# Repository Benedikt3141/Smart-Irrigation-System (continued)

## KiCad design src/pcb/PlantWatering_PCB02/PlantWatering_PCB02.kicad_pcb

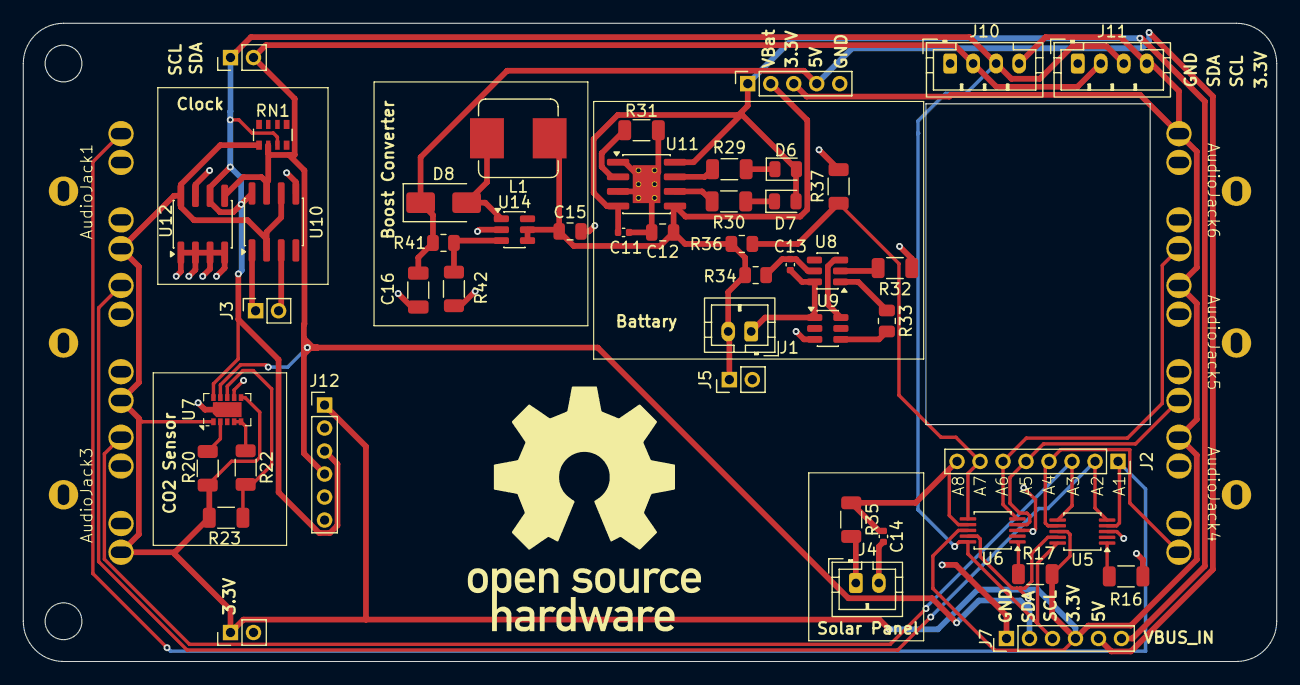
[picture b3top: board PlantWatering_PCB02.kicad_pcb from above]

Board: 2 copper layers, 109.0 x 55.5 mm, 56 parts (0 on the bottom side), 36 nets.

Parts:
AudioJack1, AudioJack2, AudioJack3, AudioJack4, AudioJack5, AudioJack6: PJ-3126-5A
C11, C13, C14: 100nF; C_0402_1005Metric
C12, C15: 10uF; C_0805_2012Metric
C16: 22uF; C_1206_3216Metric
D6: RED; LED_0805_2012Metric
D7: GREEN; LED_0805_2012Metric
D8: SS14; D_SMA
H1, H2: MountingHole; MountingHole_3.2mm_M3
J1: Battery connection; JST_PH_B2B-PH-K_1x02_P2.00mm_Vertical
J2: AnalogSignals; PinSocket_1x08_P2.00mm_Vertical
J3: 32KHZ/SQW; PinSocket_1x02_P2.00mm_Vertical
J4: Solar Panel; JST_PH_B2B-PH-K_1x02_P2.00mm_Vertical
J5: Power output; PinHeader_1x02_P2.00mm_Vertical
J6: Signal Sockets; PinSocket_1x05_P2.00mm_Vertical
J7: Connector to other Board; PinHeader_1x06_P2.00mm_Vertical
J8: I2C; PinHeader_1x02_P2.00mm_Vertical
J9: PWR_Output; PinHeader_1x02_P2.00mm_Vertical
J10, J11: I2C Pins; JST_PH_B4B-PH-K_1x04_P2.00mm_Vertical
J12: Conn_01x06_Socket; PinHeader_1x06_P2.00mm_Vertical
L1: 22uH; L_Bourns_SRP7028A_7.3x6.6mm
R16, R17, R20, R22, R31, R42: 10k; R_1206_3216Metric
R23, R37: 100k; R_1206_3216Metric
R29, R30, R32: 1k; R_1206_3216Metric
R33: 0R; R_0805_2012Metric
R34: 100; R_0805_2012Metric
R35: 4.7k; R_1206_3216Metric
R36: 220k; R_0805_2012Metric
R41: 73.2k; R_0805_2012Metric
RN1: 4.7k Resistor Array; R_Array_Convex_4x0603
U5, U6: ADS1115IDGS; TSSOP-10_3x3mm_P0.5mm
U7: CCS811; AMS_LGA-10-1EP_2.7x4mm_P0.6mm
U8: DW01A; SOT-23-6
U9: FS8205A; SOT-23-6
U10: DS3231MZ; SOIC-8_3.9x4.9mm_P1.27mm
U11: TP4056-42-ESOP8; SOIC-8-1EP_3.9x4.9mm_P1.27mm_EP2.41x3.3mm_ThermalVias
U12: AT24CS32-SSHM; SOIC-8_3.9x4.9mm_P1.27mm
U14: MT3608; SOT-23-6

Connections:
+3.3V: AudioJack1.5 (VCC), AudioJack2.5 (VCC), AudioJack3.5 (VCC), AudioJack4.5 (VCC), AudioJack5.5 (VCC), AudioJack6.5 (VCC), J6.3, J7.4, J9.1, J10.4, J11.4, J12.1, R17.2, R20.2, R23.1, RN1.1 (common), U5.8 (VDD), U6.8 (VDD), U7.1 (ADDR), U7.6 (VDD), U10.2 (VCC), U10.6 (VBAT), U12.8 (VCC)
+5V: C16.1, D8.1 (K), J6.4, J7.5, R41.1
/Analog1: AudioJack1.2 (Analog_Signal), J2.1, U5.4 (AIN0)
/Analog2: AudioJack2.2 (Analog_Signal), J2.2, U5.5 (AIN1)
/Analog3: AudioJack3.2 (Analog_Signal), J2.3, U5.6 (AIN2)
/Analog4: AudioJack4.2 (Analog_Signal), J2.4, U5.7 (AIN3)
/Analog5: AudioJack5.2 (Analog_Signal), J2.5, U6.4 (AIN0)
/Analog6: AudioJack6.2 (Analog_Signal), J2.6, U6.5 (AIN1)
/Analog7: J2.7, R36.2, R37.1, U6.6 (AIN2)
/Analog8: C14.1, J2.8, R35.1, U6.7 (AIN3)
/G1: U8.3 (OC), U9.6 (G1)
/G2: R33.2, U9.4 (G2)
/OC: R33.1, U8.1 (OD)
/S1: C13.2, J1.1, U8.6 (GND), U9.1 (S1)
/SCL: J7.3, J8.1, J10.3, J11.3, J12.3, RN1.3 (R2), U5.10 (SCL), U6.10 (SCL), U7.10 (SCL), U10.8 (SCL), U12.6 (SCL)
/SDA: J7.2, J8.2, J10.2, J11.2, J12.4, RN1.2 (R1), U5.9 (SDA), U6.9 (SDA), U7.9 (SDA), U10.7 (SDA), U12.5 (SDA)
/VBUS_IN: C11.1, D6.2 (A), D7.2 (A), J6.1, J7.6, U11.4 (V_{CC}), U11.8 (CE)
/VBat: C12.1, C15.1, J1.2, J5.1, J6.2, L1.1, R34.1, R36.1, U11.5 (BAT), U14.4 (EN), U14.5 (IN)
GND: AudioJack1.1 (GND), AudioJack2.1 (GND), AudioJack3.1 (GND), AudioJack4.1 (GND), AudioJack5.1 (GND), AudioJack6.1 (GND), C11.2, C12.2, C14.2, C15.2, C16.2, J4.2, J5.2, J6.5, J7.1, J9.2, J10.1, J11.1, J12.2, R16.2, R31.2, R32.1, R37.2, R42.2, U5.3 (GND), U6.3 (GND), U7.7 (~WAKE), U7.11 (GND), U9.3 (S2), U10.5 (GND), U11.1 (TEMP), U11.3 (GND), U11.9 (EPAD), U12.1 (A0), U12.2 (A1), U12.3 (A2), U12.4 (GND), U12.7 (WP), U14.2 (GND)
unnamed: D6.1 (K), R29.1
unnamed: D7.1 (K), R30.1
unnamed: D8.2 (A), L1.2, U14.1 (SW)
unnamed: J3.1, U10.1 (32KHZ)
unnamed: J3.2, U10.3 (~INT/SQW)
unnamed: J4.1, R35.2
unnamed: R16.1, U5.1 (ADDR)
unnamed: R17.1, U6.1 (ADDR)
unnamed: R22.2, R23.2, U7.8 (AUX)
unnamed: R22.1, U7.4 (PWM), U7.5 (Sense)
unnamed: R20.1, U7.2 (~RESET)
unnamed: R32.2, U8.2 (CS)
unnamed: C13.1, R34.2, U8.5 (VCC)
unnamed: R31.1, U11.2 (PROG)
unnamed: R29.2, U11.7 (~CHRG)
unnamed: R30.2, U11.6 (~STDBY)
unnamed: R41.2, R42.1, U14.3 (FB)

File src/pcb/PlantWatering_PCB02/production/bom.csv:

"Reference","Qty","Value","DNP","Exclude from BOM","Exclude from Board","Footprint","LCSC PN"
"AudioJack1,AudioJack2,AudioJack3,AudioJack4,AudioJack5,AudioJack6","6","","","","","ESP32_NodeMCU:PJ-3126-5A","C145816"
"C11,C13,C14","3","100nF","","","","Capacitor_SMD:C_0402_1005Metric","C1525"
"C12,C15","2","10uF","","","","Capacitor_SMD:C_0805_2012Metric","C1713"
"C16","1","22uF","","","","Capacitor_SMD:C_1206_3216Metric","C5672"
"D6","1","RED","","","","LED_SMD:LED_0805_2012Metric","C84256"
"D7","1","GREEN","","","","LED_SMD:LED_0805_2012Metric","C84260"
"D8","1","SS14","","","","Diode_SMD:D_SMA","C2480"
"L1","1","22uH","","","","Inductor_SMD:L_Bourns_SRP7028A_7.3x6.6mm","C2838326"
"R16,R17,R20,R22,R31,R42","6","10k","","","","Resistor_SMD:R_1206_3216Metric","C1489"
"R23,R37","2","100k","","","","Resistor_SMD:R_1206_3216Metric","C17900"
"R29,R30,R32","3","1k","","","","Resistor_SMD:R_1206_3216Metric","C4410"
"R33","1","0R","","","","Resistor_SMD:R_0805_2012Metric","C17477"
"R34","1","100","","","","Resistor_SMD:R_0805_2012Metric","C17408"
"R35","1","4.7k","","","","Resistor_SMD:R_1206_3216Metric","C17936"
"R36","1","220k","","","","Resistor_SMD:R_0805_2012Metric","C17556"
"R41","1","73.2k","","","","Resistor_SMD:R_0805_2012Metric","C17814"
"RN1","1","4.7k Resistor Array","","","","Resistor_SMD:R_Array_Convex_4x0603","C1980"
"U5,U6","2","ADS1115IDGS","","","","Package_SO:TSSOP-10_3x3mm_P0.5mm","C37593"
"U8","1","DW01A","","","","Package_TO_SOT_SMD:SOT-23-6","C351410"
"U9","1","FS8205A","","","","Package_TO_SOT_SMD:SOT-23-6","C908265"
"U10","1","DS3231MZ","","","","Package_SO:SOIC-8_3.9x4.9mm_P1.27mm","C107410"
"U11","1","TP4056-42-ESOP8","","","","Package_SO:SOIC-8-1EP_3.9x4.9mm_P1.27mm_EP2.41x3.3mm_ThermalVias","C16581"
"U12","1","AT24CS32-SSHM","","","","Package_SO:SOIC-8_3.9x4.9mm_P1.27mm","C615972"
"U14","1","MT3608","","","","Package_TO_SOT_SMD:SOT-23-6","C84817"

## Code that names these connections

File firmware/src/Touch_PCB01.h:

#pragma once

#include <Arduino.h>

class TFT_eSPI;

class Touch_PCB01 {
public:
    struct RawPoint {
        int16_t x = 0;
        int16_t y = 0;
        int16_t z = 0;
        bool valid = false;
    };

    struct Point {
        int16_t x = 0;
        int16_t y = 0;
        int16_t z = 0;
        bool touched = false;
    };

    struct Calibration {
        // raw -> native display coordinates (rotation 0)
        float xFromRawX = 1.0f;
        float xFromRawY = 0.0f;
        float xOffset   = 0.0f;
        float yFromRawX = 0.0f;
        float yFromRawY = 1.0f;
        float yOffset   = 0.0f;
        bool valid = false;
    };

    // PCB01 / common 2.4" UNO resistive TFT shield wiring:
    // XP = LCD_D6 = GPIO27
    // YM = LCD_D7 = GPIO14
    // YP drive = LCD_WR = GPIO4, analog sense = GPIO39 (ADC1)
    // XM drive = LCD_RS = GPIO15, analog sense = GPIO35 (ADC1)
    Touch_PCB01(
        uint8_t xp = 27,
        uint8_t ym = 14,
        uint8_t ypDrive = 4,
        uint8_t ypSense = 39,
        uint8_t xmDrive = 15,
        uint8_t xmSense = 35,
        uint8_t tftCs = 33,
        uint16_t nativeWidth = 240,
        uint16_t nativeHeight = 320
    );

    // Call after tft.begin(). Keep this rotation equal to TFT_eSPI's rotation.
    void begin(uint8_t rotation = 1);
    void setRotation(uint8_t rotation);
    uint8_t rotation() const { return _rotation; }

    uint16_t width() const;
    uint16_t height() const;

    // Pressure threshold for a valid touch. Typical starting point: 150..300.
    void setPressureThreshold(uint16_t threshold) { _pressureThreshold = threshold; }
    uint16_t pressureThreshold() const { return _pressureThreshold; }

    // Raw measurements, independent of calibration/rotation.
    RawPoint getRawPoint();
    bool isTouched();

    // Returns true only when a valid calibrated touch is present.
    bool getPoint(Point &point);
    Point getPoint();

    void setCalibration(const Calibration &calibration);
    const Calibration &calibration() const { return _calibration; }
    bool isCalibrated() const { return _calibration.valid; }
    void clearCalibration();

    // Interactive 5-point calibration. Calibration is stored in RAM.
    // Optionally call saveCalibration() afterwards.
    bool calibrate(TFT_eSPI &tft, Print &log = Serial);

#if defined(ESP32)
    // ESP32 NVS storage. Namespace must be <= 15 characters.
    bool saveCalibration(const char *nameSpace = "touchPCB01") const;
    bool loadCalibration(const char *nameSpace = "touchPCB01");
    bool eraseSavedCalibration(const char *nameSpace = "touchPCB01");
#endif

private:
    static constexpr uint8_t ADC_BITS = 12;
    static constexpr int ADC_MAX_VALUE = (1 << ADC_BITS) - 1;
    static constexpr uint8_t ADC_SAMPLES = 5; // odd number for median

    uint8_t _xp;
    uint8_t _ym;
    uint8_t _ypDrive;
    uint8_t _ypSense;
    uint8_t _xmDrive;
    uint8_t _xmSense;
    uint8_t _tftCs;

    uint16_t _nativeWidth;
    uint16_t _nativeHeight;
    uint8_t _rotation = 1;
    uint16_t _pressureThreshold = 180;

    Calibration _calibration;

    int _savedCsLevel = HIGH;

    void selectTouchBus();
    void restoreTftBus();

    int16_t readMedianAdc(uint8_t pin);
    int16_t readRawX();
    int16_t readRawY();
    int16_t readPressure();

    void nativeToScreen(float nativeX, float nativeY, float &screenX, float &screenY) const;
    void screenToNative(float screenX, float screenY, float &nativeX, float &nativeY) const;

    static bool solve3x3(float a[3][3], float b[3], float out[3]);
    bool fitAffine(const RawPoint raw[], const float nativeX[], const float nativeY[], size_t count);

    RawPoint waitForStablePress(Print &log);
    void waitForRelease();
    static void drawCrosshair(TFT_eSPI &tft, int16_t x, int16_t y, uint16_t color);
};

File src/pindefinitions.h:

// ********** I2C Pins *********
#ifndef SCL
#define SCL 22
#endif

#ifndef SDA
#define SDA 21
#endif

#ifndef ADDR_ADC1
#define ADDR_ADC1 0x4B
#endif

#ifndef ADDR_ADC2
#define ADDR_ADC2 0x48
#endif

#ifndef ADDR_CLOCK1
#define ADDR_CLOCK1 0x57 
#endif

#ifndef ADDR_CLOCK2
#define ADDR_CLOCK2 0x68 
#endif

#ifndef ADDR_BMP280
#define ADDR_BMP280 0x76
#endif

#ifndef ADDR_BMP180
#define ADDR_BMP180 0x77
#endif


// ********* SPI Pins *********
#ifndef MOSI
#define MOSI 23
#endif

#ifndef MISO
#define MISO 19
#endif

#ifndef SCL_SPI
#define SCL_SPI 18
#endif

#ifndef CS_SD
#define CS_SD 5
#endif


// ********* Analog Signal Pins ********
#ifndef MQ_SENSOR_PIN
#define MQ2_SENSOR_PIN 34 // Analog 9
#endif

#ifndef ANALOG10
#define ANALOG10 35 // Display Touch
#endif

#ifndef BUTTONS 
#define BUTTONS 36 // Analog 11
#endif

#ifndef ANALOG12
#define ANALOG12 39 // Display Touch
#endif


// ******** LCD Display Pins ******** //actually they're configured in .pio\libdeps\az-delivery-devkit-v4\TFT_eSPI\User_Setups. It's just for clarification :)
#ifndef LCD_Pins 

    // Control Pins
    #define TFT_CS   33
    #define TFT_DC   15   // LCD_RS
    #define TFT_RST  -1
    #define TFT_WR    4
    #define TFT_RD    2

    // 8-Bit-Databus
    #define TFT_D0   12
    #define TFT_D1   13
    #define TFT_D2   26
    #define TFT_D3   25
    #define TFT_D4   17
    #define TFT_D5   16
    #define TFT_D6   27
    #define TFT_D7   14

#endif


// ********** LED Strip ********
#ifndef LED_PIN
#define LED_PIN 32
#endif

#ifndef NUMBER_LEDS
#define NUMBER_LEDS 8
#endif

// ********** Screensaver Video ********
#ifndef SCREENSAVER_VIDEO_FILE_NAME
#define  SCREENSAVER_VIDEO_FILE_NAME "Lizard.mjpeg";
#endif

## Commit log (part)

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2026-06-12 First System lastly added the RTC module
2026-06-12 modified Pins and changed TFT configuration, moved TFT Configuration from .pio to visible folder and changed library for touch functions of the tft according to pindefinitions.h
2026-06-15 changed pin configuration so now display and leds work fine
2026-06-15 added the SD checker
2026-06-15 added MQ2-Sensor
2026-06-15 added BMP280
2026-06-26 added buttons and interrupts
2026-06-26 added the pcb files from other directory
2026-06-26 Add project title to README
2026-06-27 added readme text
2026-06-27 added images
2026-06-27 tried to fix images
2026-06-27 finally fixed images
2026-06-27 added Concept drawings
2026-06-28 changed PCB01
2026-06-28 modified PCB02 for 2Layer board in order to save money
2026-06-28 update PDF and added labels to PCB02
2026-06-28 added Journal
2026-06-28 corrected Spelling with AI
2026-06-29 addedcontent to Journal and fixed AI slop
2026-06-29 changed resistance of buttons (look at schematic)
2026-06-29 cleaned up button code
2026-06-30 added screensaver
2026-06-30 changed code for my needs
2026-06-30 added content to Journal
2026-06-30 actually added content to Journal
